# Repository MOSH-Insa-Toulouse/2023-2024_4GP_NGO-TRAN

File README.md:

# 2023-2024 : Capteur low-tech Graphite (Tan Anh Khoa NGO &amp; Le Duc Minh TRAN)

## SOMMAIRE
*** 
  - [Contexte](#contexte)
  - [Livrables](#livrables)
  - [Matériel nécessaire](#matériel-nécessaire)
  - [1. Simulation électronique du capteur sous LTSpice](#simulation-électronique-du-capteur-sous-ltspice)
  - [2. Design du PCB sous KiCad](#design-du-pcb-sous-kicad)
  - [3. Code arduino](#code-arduino)
  - [4. Application android APK sous MIT App Inventor](#application-android-apk-sous-mit-app-inventor)
  - [5. Réalisation du shield](#réalisation-du-shield)
  - [6. Banc de test](#banc-de-test)
  - [7. Datasheet](#datasheet)
  - [Contact](#contact) 

*** 

## Contexte
&nbsp;&nbsp;&nbsp;&nbsp;&nbsp;&nbsp;Dans le cadre de l'unité de formation "Du capteur au banc de test" dispensée en 4ème année du cursus Génie Physique à l'INSA Toulouse, notre équipe a conçu un dispositif de mesure de contrainte innovant. L'inspiration pour le capteur de ce dispositif provient de l'article scientifique "Pencil Drawn Strain Gauges and Chemiresistors on Paper" (Cheng-Wei Lin*, Zhibo Zhao*, Jaemyung Kim & Jiaxing Huang). Ce capteur, d'une simplicité remarquable, est constitué d'un morceau de papier sur lequel du graphite est appliqué à l'aide d'un crayon à papier. 

&nbsp;&nbsp;&nbsp;&nbsp;&nbsp;&nbsp;Le principe de fonctionnement repose sur l'observation que la déformation du papier entraîne une variation du nombre de particules de graphite interconnectées. Cette modification de la structure granulaire du graphite se traduit par une variation de la résistance et de la conductance du capteur. En exploitant cette propriété, il devient possible de remonter à la déformation subie, à l'instar d'une jauge de contrainte classique.

&nbsp;&nbsp;&nbsp;&nbsp;&nbsp;&nbsp;Notre objectif principal était de développer un dispositif de mesure de déformation basé sur un capteur low-tech. Pour atteindre cet objectif, nous avons suivi une démarche structurée comprenant plusieurs étapes clés : simulations électroniques pour valider le concept, conception du circuit imprimé (PCB) pour intégrer le capteur, développement du code Arduino pour l'acquisition et le traitement des données, et enfin, réalisation de la fiche technique du dispositif.

## Livrables
Les livrables de ce projet sont les suivants :
  
* Un shield PCB personnalisé connecté à une carte Arduino UNO. Ce shield intègre :
     
   - Un capteur de contrainte innovant à base de graphite.
   - Un amplificateur à transimpédance pour traiter le signal du capteur.
   - Un module Bluetooth pour la communication sans fil.
   - Un écran OLED pour l'affichage des données (ajouté pour améliorer l'expérience utilisateur).
   - Un capteur de flexion commercial pour comparaison (ajouté à des fins de validation).
   - Un potentiomètre numérique pour ajuster le gain de l'amplificateur (ajouté pour plus de flexibilité).
   - Un encodeur rotatif pour basculer entre les mesures des capteurs (ajouté pour faciliter la comparaison).
  
* Code Arduino     
   - L'acquisition des mesures de contrainte du capteur graphite.
   - La connexion et la communication Bluetooth.
   - L'affichage des données sur l'écran OLED.
   - Le réglage du gain via le potentiomètre numérique.
   - La sélection du capteur actif avec l'encodeur rotatif.
   - Réaliser des essais de banc de test rigoureux.
   - Évaluer les performances du capteur de contrainte graphite.
  
* Une application Android intuitive (APK) (développée avec MIT App Inventor) qui :
   - Permet de visualiser les données en temps réel.
   - Offre une interface conviviale pour interagir avec le système.

* Une datasheet complète qui détaille :
   - Les caractéristiques techniques du capteur graphite.
   - Son principe de fonctionnement.
   - Les instructions d'utilisation et de calibration.
   - Les résultats des tests de performance.

## Matériel nécessaire
Pour réaliser notre dispositif électronique, voici la liste des composants nécessaires :

- Résistances : 1 de 1 $k\ohm$, 1 de $10k\ohm$, 2 de $100k\ohm$ pour l'amplificateur transimpédance. 3 de $10k\ohm$ pour les boutons (peuvent être éviter en utilisant les résistances internes de l'arduino) et 1 de $33k\ohm$ pour le flex sensor.
- Capacités : 3 de 100 nF, 1 de 1 uF
- Arduino Uno
- Amplificateur opérationnel LTC1050
- Potentiomètre digital MCP41050
- Module Bluetooth HC05
- Ecran OLED 128x64
- Flex Sensor
- Encodeur rotatif KY-040

## Simulation électronique du capteur sous LTSpice
&nbsp;&nbsp;&nbsp;&nbsp;&nbsp;&nbsp;Pour amplifier le signal de notre capteur de graphite, caractérisé par une résistance élevée et un courant de sortie faible, nous avons conçu un montage à transimpédance. Ce montage, basé sur un amplificateur opérationnel (AOP), permet de convertir le faible courant en une tension exploitable par le convertisseur analogique-numérique (ADC) de l'Arduino UNO. \
&nbsp;&nbsp;&nbsp;&nbsp;&nbsp;&nbsp;La conception du circuit a été simulée sur LTspice, en suivant un [schéma spécifique](Image/LTspice/schema_suggere.png). Le choix de l'AOP s'est porté sur le LTC 1050, reconnu pour sa capacité à gérer des courants d'entrée faibles et son faible offset de tension, garantissant ainsi la précision des mesures. Voici son schéma :

Afin d'optimiser la qualité du signal, trois filtres ont été intégrés au circuit :

- Un filtre passe-bas passif (R1, C1) à l'entrée, avec une fréquence de coupure de 16 Hz, pour atténuer les bruits en courant.
- Un filtre passe-bas actif (R3, C4) couplé à l'AOP, avec une fréquence de coupure de 1,6 Hz, pour filtrer le bruit à 50 Hz du réseau électrique.
- Un filtre passe-bas (R6, C2) à la sortie de l'AOP, avec une fréquence de coupure de 1,6 kHz, pour éliminer les bruits générés lors du traitement du signal.

De plus, des composants supplémentaires ont été ajoutés pour améliorer la robustesse du circuit :
- La capacité C3 pour filtrer le bruit de l'alimentation.
- La résistance R5 pour protéger l'AOP contre les décharges électrostatiques et former un filtre passe-bas avec C1 pour les bruits en tension.
- La résistance R2, qui sera remplacée par un potentiomètre numérique pour ajuster le gain de l'AOP selon les besoins.

Les tests effectués sur le circuit simulé ont confirmé l'efficacité des filtres.

Voici la réponse de notre circuit pour vérfier que le capteur soit correctement amplifié : 

Le signal amplifié atteint 1V, une valeur compatible avec l'Arduino UNO.

De plus, la simulation d'un courant alternatif a démontré une atténuation significative du bruit, notamment une réduction d'environ 72 dB à 50 Hz.

## Design du PCB sous KiCad

Pour développer notre circuit imprimé (PCB), nous avons utilisé le logiciel KiCad 7.0 et avons reproduit le schéma électrique initial, en y apportant quelques modifications. La résistance R2 a été remplacée par un potentiomètre numérique pour permettre le réglage du gain de l'AOP.

Afin d'optimiser les capacités de mesure et de comparaison de notre capteur graphite, nous avons intégré plusieurs composants supplémentaires :

- GrapheSenso (notre capteur graphite) pour mesurer les variations de résistance.
- Un flex sensor commercial servant de référence pour comparer les résultats.

- Un module Bluetooth HC-05 pour établir une communication sans fil avec une application mobile dédiée.
- Un écran OLED pour visualiser les mesures en temps réel.
- Un encodeur rotatif pour basculer facilement entre les deux capteurs dans l'interface de l'application.

Tous ces composants ont été soigneusement disposés sur un shield Arduino UNO pour faciliter l'intégration et l'utilisation.

La première étape de la conception du PCB a consisté à créer les symboles des différents composants et à reproduire le schéma électrique complet dans KiCad. Le schéma final intègre tous les éléments mentionnés ci-dessus.

Ensuite, nous avons réalisé les empreintes des composants pour les placer sur le PCB. L'un des défis majeurs a été d'optimiser le placement pour éviter les vias, en particulier pour la connexion à la masse (GND). Le résultat final est un PCB compact et fonctionnel.

Une visualisation 3D du PCB a été générée pour vérifier le routage et l'agencement des composants. Cette étape a permis de s'assurer de la faisabilité de la fabrication du PCB.

Toutes les ressources utilisées pour la conception du PCB, y compris les empreintes, le schéma et les fichiers de conception, sont disponibles dans notre dossier KiCad.

## Code Arduino

&nbsp;&nbsp;&nbsp;&nbsp;&nbsp;&nbsp;Notre [programme Arduino](Arduino/Projet_Capteur_Final.ino) permet de mesurer la résistance du capteur en graphène et du flex sensor en convertissant les valeurs de tension obtenues par l'ADC de l'Arduino. Les valeurs de résistance sélectionnées sont ensuite affichées sur l'écran OLED, la sélection étant contrôlée par l'encodeur rotatif.

&nbsp;&nbsp;&nbsp;&nbsp;&nbsp;&nbsp;Le programme établit également une communication bidirectionnelle entre le module Bluetooth et l'application mobile. Des protocoles spécifiques ont été mis en place pour gérer l'échange de données et de commandes. Le module Bluetooth reçoit les instructions de l'application mobile, telles que la demande de données ou le réglage de la résistance du potentiomètre numérique, et transmet les données mesurées en retour.

&nbsp;&nbsp;&nbsp;&nbsp;&nbsp;&nbsp;Une fonctionnalité notable de notre programme est la possibilité de régler le gain de l'amplificateur en modifiant la valeur de résistance du potentiomètre numérique via l'interface de l'application mobile. Cette flexibilité permet d'adapter le système à différentes conditions de mesure.

## Application android APK sous MIT App Inventor
&nbsp;&nbsp;&nbsp;&nbsp;&nbsp;&nbsp;Une application est également disponible avec le dispositif : développé sous [MIT App Inventor](https://appinventor.mit.edu/) . 

&nbsp;&nbsp;&nbsp;&nbsp;&nbsp;&nbsp;L'application reçoit les données transmis par le module bluetooth HC-05. Elle affiche ensuite la valeur tranmis (des $M\ohm$ pour le capteur graphite ou des $\ohm$ pour le flex sensor.

&nbsp;&nbsp;&nbsp;&nbsp;&nbsp;&nbsp;L'application peut s'installer [sous android ici](apk/First_application_copy.apk) et toutes les informations liées à l'application son dans [le dossier Application Android](apk).

### Résumé des particularités de nos programmes et applications
&nbsp;&nbsp;&nbsp;&nbsp;&nbsp;&nbsp;Nos programmes et applications se distinguent par une optimisation supérieure à celle d'autres projets. Nous utilisons 2 octets de données pour la transmission, préservant ainsi la résolution et simplifiant la programmation de l'encodeur rotatif, contrairement à d'autres projets qui utilisent 1 octet et sacrifient la résolution.

&nbsp;&nbsp;&nbsp;&nbsp;&nbsp;&nbsp;De plus, notre application développée sur la plateforme du MIT emploie la commande "read" pour vider le tampon avant la lecture des données, garantissant ainsi la fiabilité des données lues et l'affichage précis des graphiques.

## Réalisation du shield

&nbsp;&nbsp;&nbsp;&nbsp;&nbsp;&nbsp;Dans le cadre de notre projet, nous avons réalisé la fabrication d'un circuit imprimé (PCB) au sein des départements de Génie Électrique et Informatique et de Génie Physique de l'INSA Toulouse. Après avoir conçu le circuit sur le logiciel KICAD, nous avons confié l'impression à Cathy.

&nbsp;&nbsp;&nbsp;&nbsp;&nbsp;&nbsp;Le processus de fabrication a débuté par l'impression de notre modèle sur du papier calque, qui a ensuite servi de masque pour l'insolation UV d'une plaquette d'époxy cuivrée. L'exposition aux UV a duré une dizaine de minutes, après quoi la résine non exposée a été éliminée à l'aide d'un révélateur. La plaquette a ensuite été plongée dans un bain de perchlorure de fer pendant 7 à 9 minutes pour dissoudre le cuivre non protégé, révélant ainsi les pistes du circuit. Un rinçage à l'acétone a finalisé le processus, nous permettant d'obtenir un PCB conforme à notre conception initiale.

&nbsp;&nbsp;&nbsp;&nbsp;&nbsp;&nbsp;Une fois le PCB fabriqué, nous avons procédé à son assemblage. Cela a nécessité le perçage de trous de deux tailles différentes, 0,8 mm et 1 mm, selon les spécifications de notre projet KICAD. Les trous de 0,8 mm ont été utilisés pour les composants tels que les AOP LTC1050, les résistances et les condensateurs, tandis que les trous de 1 mm ont servi pour les broches de connexion de l'Arduino Uno et les headers des modules OLED, Bluetooth et encodeur rotatif. Après le perçage, nous avons soudé les composants en place à l'aide d'étain pour garantir des connexions électriques solides.

&nbsp;&nbsp;&nbsp;&nbsp;&nbsp;&nbsp;Nous tenons à remercier chaleureusement Cathy pour son aide précieuse dans la réalisation de notre PCB. Son expertise et son soutien ont été essentiels pour mener à bien cette étape cruciale de notre projet.

## Banc de test

&nbsp;&nbsp;&nbsp;&nbsp;&nbsp;&nbsp;Afin de caractériser notre capteur et son montage transimpédance, nous avons opté pour des demi-cercles imprimés en 3D de diamètres croissants (de 2 cm à 5 cm par incréments de 0,5 cm). Cette configuration nous permet d'évaluer l'évolution de la résistance électrique en fonction de la déformation appliquée.

&nbsp;&nbsp;&nbsp;&nbsp;&nbsp;&nbsp; Grâce à ces demis-cercles, nous allons pouvoir calculer la variation de la résistance électrique $\frac{\Delta R}{R_0}$ en fonction de la déformation $\epsilon=\frac{e}{D}$. Nous avons ici mesuré notre épaisseur de notre papier $e=0.2 mm$. ALes mesures effectuées sur papier d'épaisseur constante (0,1 mm pour le plus petit diamètre, 0,04 mm pour le plus grand) révèlent des courbes caractéristiques distinctes pour les crayons 2B, B et HB, en tension comme en compression.

&nbsp;&nbsp;&nbsp;&nbsp;&nbsp;&nbsp;Nous observons une augmentation de la résistance en tension (éloignement des atomes de carbone) et une diminution en compression (rapprochement des atomes). De plus, la variation relative de résistance est inversement proportionnelle à la quantité de carbone présente dans le crayon (2H < H < HB < B < 2B).

&nbsp;&nbsp;&nbsp;&nbsp;&nbsp;&nbsp;Contrairement aux travaux de Cheng-Wei Lin et al. ("Pencil Drawn Strain Gauges and Chemiresistors on Paper"), nous avons réussi à mesurer la résistance avec un crayon 2H.

&nbsp;&nbsp;&nbsp;&nbsp;&nbsp;&nbsp;En comparaison avec un capteur de flexion commercial, notre dispositif semble moins sensible et moins résistant aux fortes déformations, limitant son nombre d'utilisations, cependant, ils peuvent être utilisés dans deux directions, ce qui constitue une nette amélioration par rapport aux capteurs commerciaux utilisés dans une seule direction.

&nbsp;&nbsp;&nbsp;&nbsp;&nbsp;&nbsp;Il est important de noter que ces résultats sont à interpréter avec prudence, compte tenu des conditions expérimentales variables (quantité de graphite déposée, méthode de déformation).

&nbsp;&nbsp;&nbsp;&nbsp;&nbsp;&nbsp;Pour améliorer la reproductibilité, nous recommandons l'utilisation d'un servo-moteur pour contrôler précisément la déformation et la quantité de graphite déposée. Alternativement, des cercles de diamètres connus pourraient être reproduits avec des déformations plus faibles pour préserver l'intégrité du capteur.

## Datasheet

&nbsp;&nbsp;&nbsp;&nbsp;&nbsp;&nbsp; Vous pouvez retrouver la datasheet du produit [ici](datasheet/Datasheet-GrapheSenso.pdf).

## Contact

&nbsp;&nbsp;&nbsp;&nbsp;&nbsp;&nbsp;Vous pouvez nous contacter pour toutes questions :
- Tan Anh Khoa NGO : takngo@insa-toulouse.fr
- Le Duc Minh TRAN : ltra@insa-toulouse.fr

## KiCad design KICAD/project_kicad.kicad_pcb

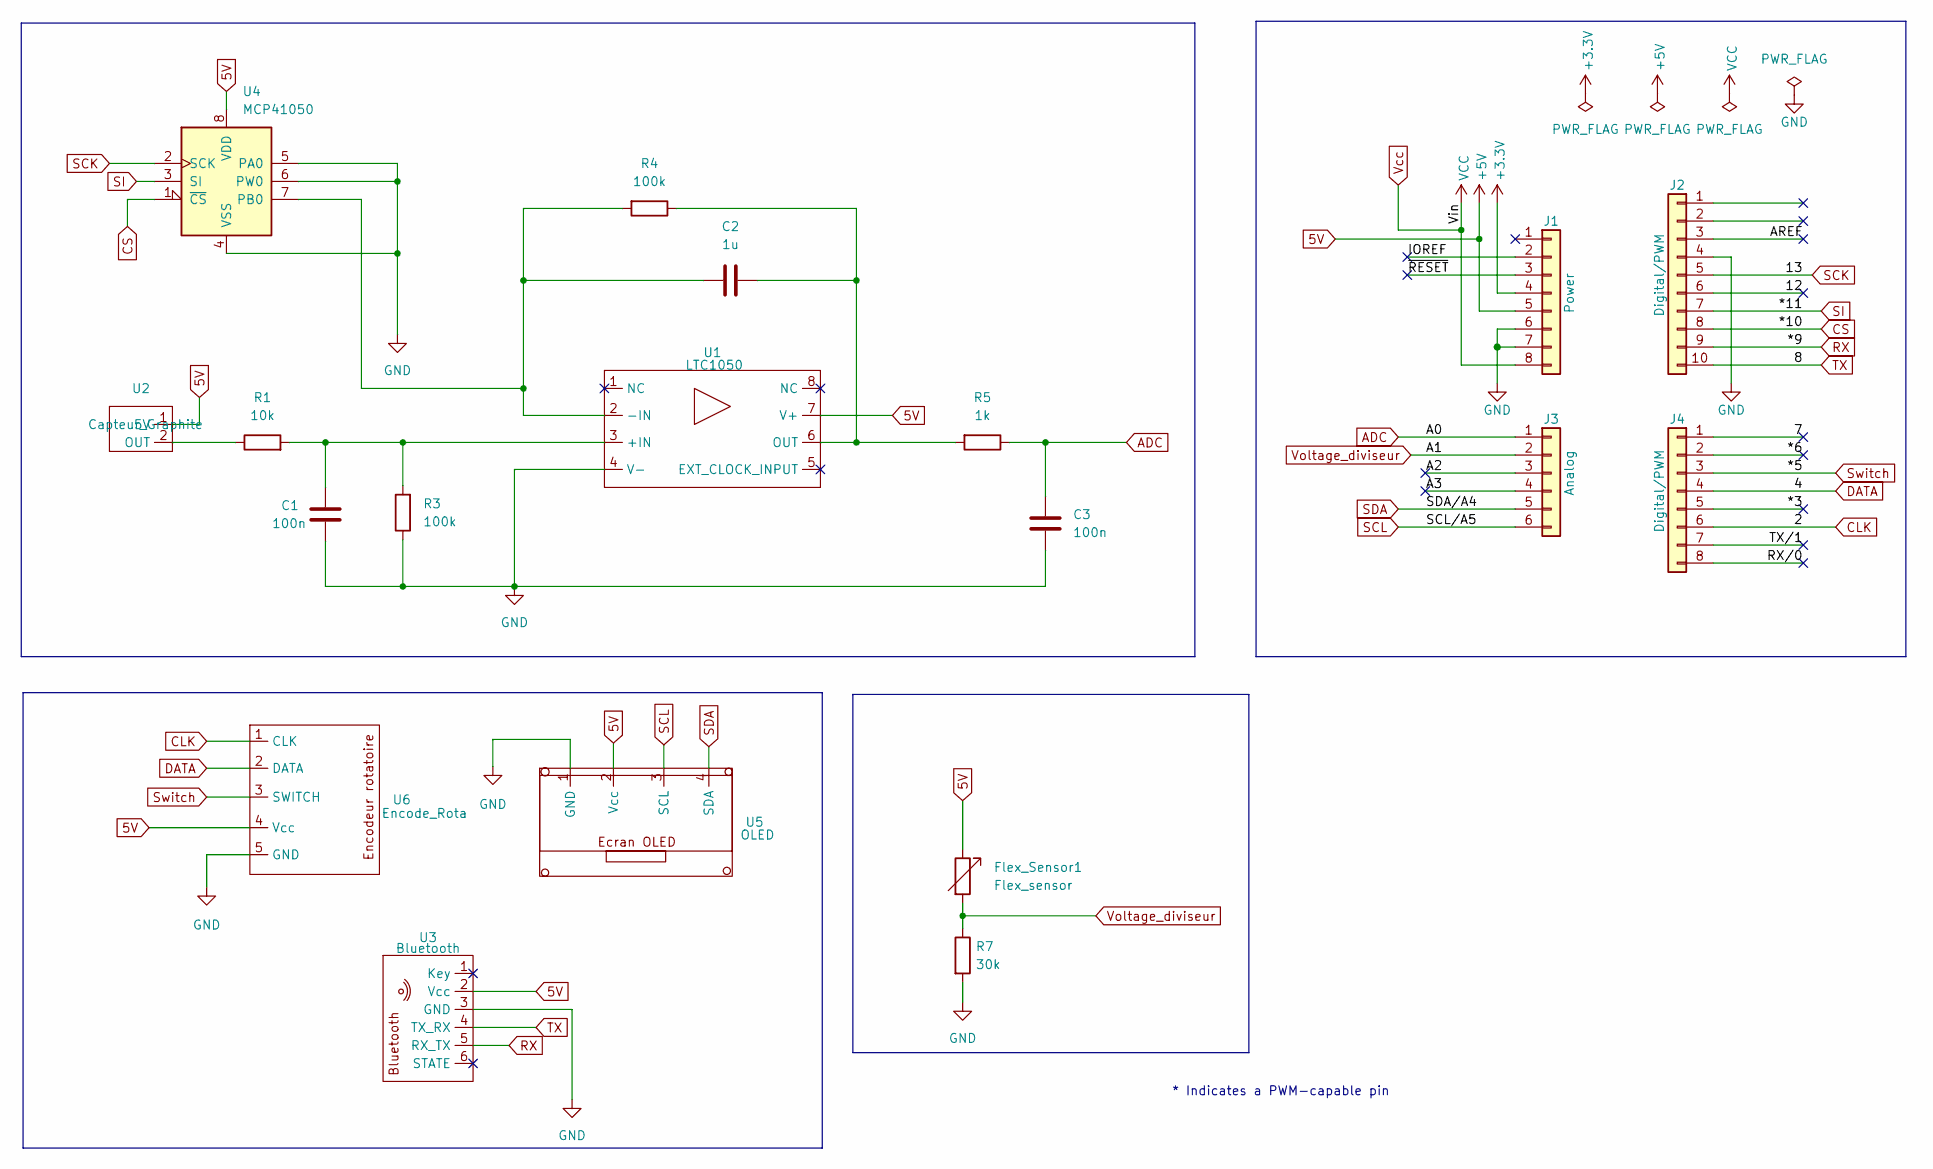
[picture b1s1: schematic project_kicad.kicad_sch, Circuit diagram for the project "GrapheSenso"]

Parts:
C1, C3: 100n; CP_Radial_Tantal_D5.5mm_P2.50mm
C2: 1u; C_Rect_L7.0mm_W4.5mm_P5.00mm
Flex_Sensor1: Flex_sensor; Flex
J1: Power; PinSocket_1x08_P2.54mm_Vertical
J2: Digital/PWM; PinSocket_1x10_P2.54mm_Vertical
J3: Analog; PinSocket_1x06_P2.54mm_Vertical
J4: Digital/PWM; PinSocket_1x08_P2.54mm_Vertical
R1: 10k; R_Axial_DIN0204_L3.6mm_D1.6mm_P5.08mm_Horizontal
R3, R4: 100k; R_Axial_DIN0204_L3.6mm_D1.6mm_P5.08mm_Horizontal
R5: 1k; R_Axial_DIN0204_L3.6mm_D1.6mm_P5.08mm_Horizontal
R7: 30k; R_Axial_DIN0204_L3.6mm_D1.6mm_P5.08mm_Horizontal
U1: LTC1050
U2: Capteur_Graphite; Capteur Graphite
U3: Bluetooth; Bluetooth HC05-20
U4: MCP41050; Pot_Digital
U5: OLED; Ecran OLED
U6: Encode_Rota; Encodeur rotatoire

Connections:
5V: Flex_Sensor1.1, J1.5, U1.7 (V+), U2.1 (5V), U3.2 (Vcc), U4.8 (VDD), U5.2 (Vcc), U6.4 (Vcc)
+3V3: J1.4
/7: J4.1
/12: J2.6
/*3: J4.5
/*6: J4.2
/A2: J3.3
/A3: J3.4
/AREF: J2.3
/IOREF: J1.2
/RX/0: J4.8
/TX/1: J4.7
/~RESET: J1.3
ADC: C3.2, J3.1, R5.1
CLK: J4.6, U6.1 (CLK)
CS: J2.8, U4.1 (~CS)
DATA: J4.4, U6.2 (DATA)
GND: C1.1, C3.1, J1.6, J1.7, J2.4, R3.1, R7.2, U1.4 (V-), U3.3 (GND), U4.4 (VSS), U4.5 (PA0), U4.6 (PW0), U5.1 (GND), U6.5 (GND)
unnamed: C1.2, R1.2, R3.2, U1.3 (+IN)
unnamed: C2.2, R4.2, U1.2 (-IN), U4.7 (PB0)
unnamed: C2.1, R4.1, R5.2, U1.6 (OUT)
unnamed: R1.1, U2.2 (OUT)
RX: J2.9, U3.5 (RX_TX)
SCK: J2.5, U4.2 (SCK)
SCL: J3.6, U5.3 (SCL)
SDA: J3.5, U5.4 (SDA)
SI: J2.7, U4.3 (SI)
Switch: J4.3, U6.3 (SWITCH)
TX: J2.10, U3.4 (TX_RX)
Vcc: J1.8
Voltage_diviseur: Flex_Sensor1.2, J3.2, R7.1

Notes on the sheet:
* Indicates a PWM-capable pin

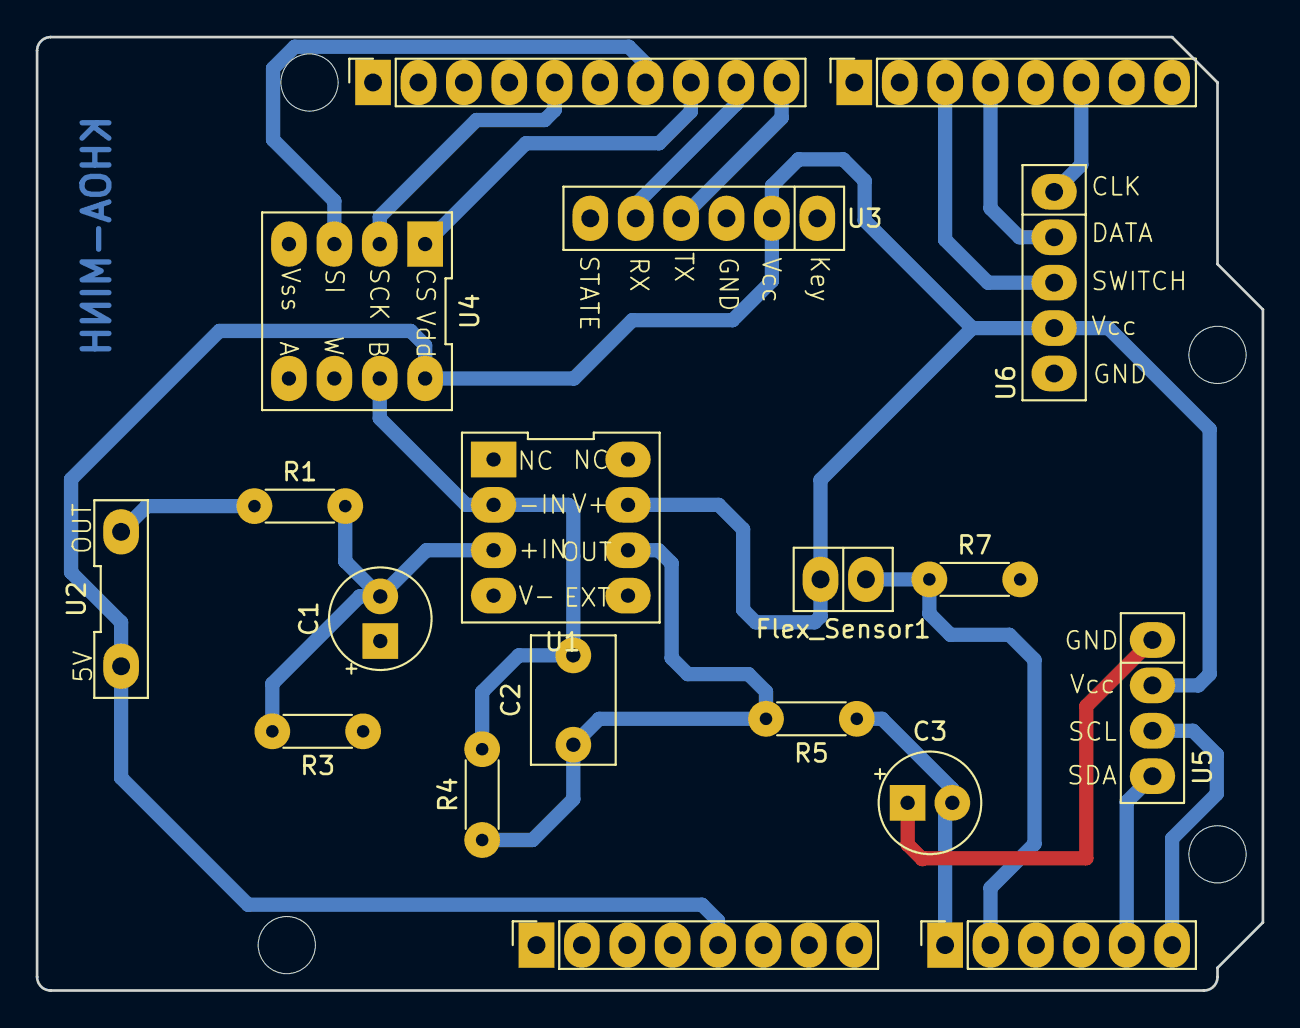
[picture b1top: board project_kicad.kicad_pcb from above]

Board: 2 copper layers, 68.6 x 53.3 mm, 23 parts (0 on the bottom side), 18 nets.

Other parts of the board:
MH1, MH2, MH3, MH4: MountingHole_3.2mm

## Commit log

2024-06-06 Create PCB
